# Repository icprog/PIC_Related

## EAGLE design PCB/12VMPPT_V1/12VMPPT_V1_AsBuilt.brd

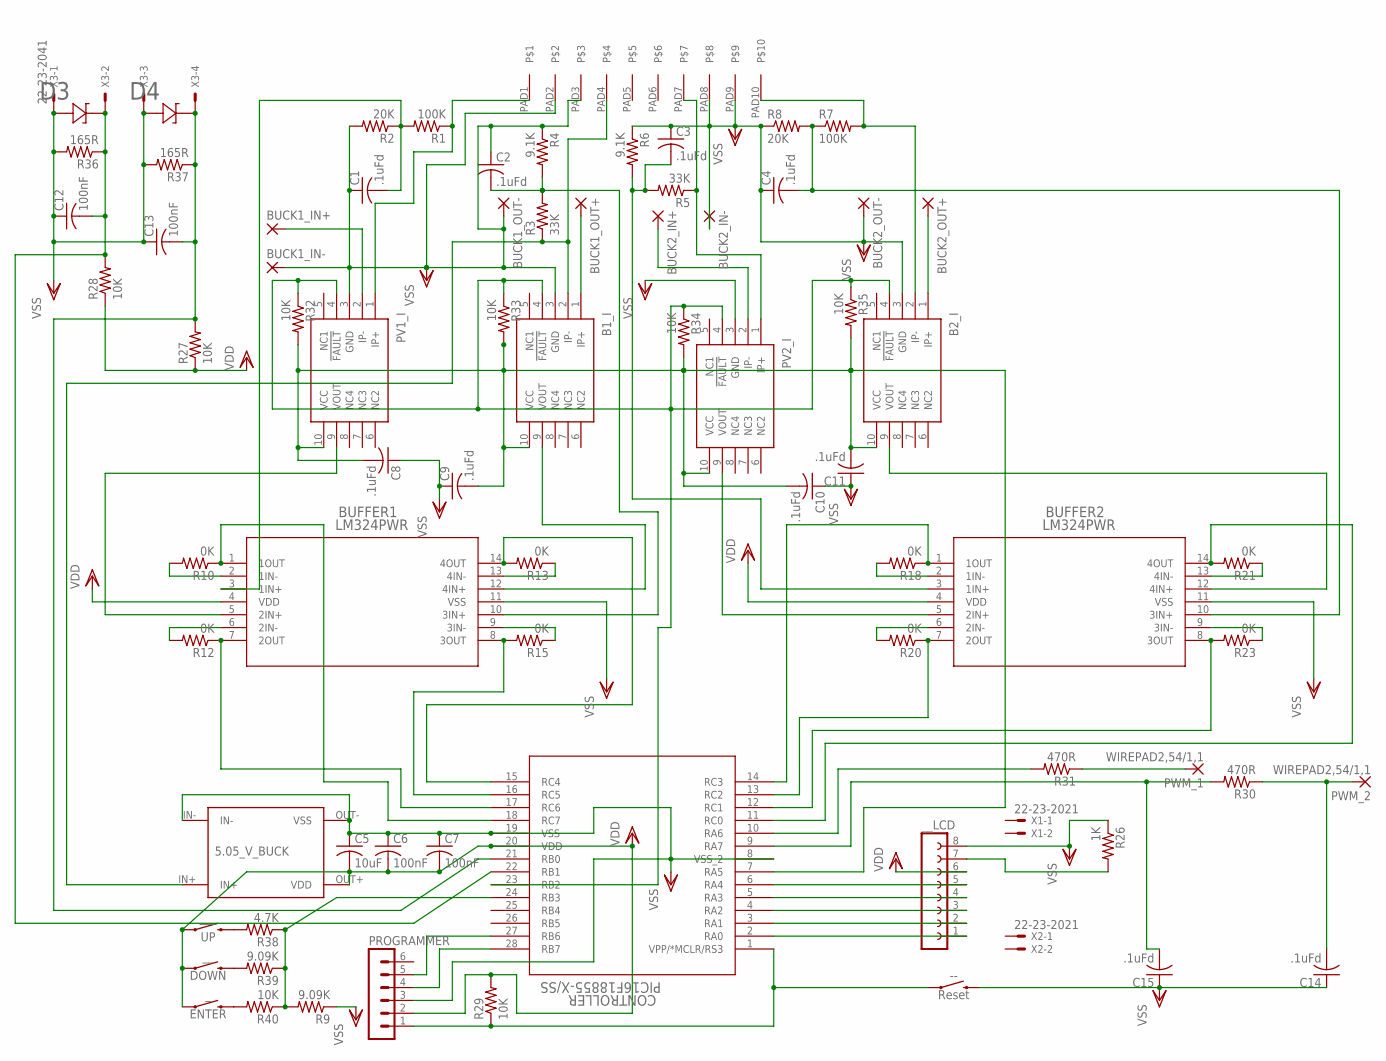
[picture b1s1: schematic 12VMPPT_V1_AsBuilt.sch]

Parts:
5.05_V_BUCK: TINY_BUCK
--: Reset; TACTILE_SWITCH_PTH_6.0MM
B1_I, B2_I: ACS711KEXLT-15AB-T; EX-PACKAGE
BUCK1_IN+, BUCK1_IN-, BUCK1_OUT+, BUCK1_OUT-, BUCK2_IN+, BUCK2_IN-, BUCK2_OUT+, BUCK2_OUT-: 3,81/1,4
BUFFER1, BUFFER2: LM324PWR; PW14
C1, C2, C3, C4, C8, C9, C10, C11, C14, C15: .1uFd; C0603
C5: 10uF; C0603
C6, C7, C12, C13: 100nF; C0603
CONTROLLER: PIC16F18855-X/SS; SSOP28_MC
D3, D4: CZRU52C3V3; CZRU
PROGRAMMER: MA06-1
PV1_I, PV2_I: ACS711KEXLT-15AB-T; EX-PACKAGE
PWM_1, PWM_2: WIREPAD2,54/1,1; 2,54/1,1
R1, R7: 100K; R0603
R2, R8: 20K; R0603
R3: 33K; R0603
R4, R6: 9.1K; R0603
R5: 33K; R1206
R9, R39: 9.09K; R0603
R10, R12, R13, R15, R18, R20, R21, R23: 0K; R0603
R26: 1K; R0603
R27, R32, R33: 10K; R1206
R28, R29, R34, R35, R40: 10K; R0603
R30: 470R; R0603
R31: 470R; R1206
R36, R37: 165R; R0603
R38: 4.7K; R0603
U$1: CONN-KF2EDG-10(5.08)E-BAYPLUGGABLECONNECTORS; CONN-KF2EDG-10(5.08)
X1, X2: 22-23-2021
X3: 22-23-2041
_: ENTER; TACTILE_SWITCH_PTH_6.0MM
__: DOWN; TACTILE_SWITCH_PTH_6.0MM
__LCD: FE08
___: UP; TACTILE_SWITCH_PTH_6.0MM

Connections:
BUCK_1OUT+: 5.05_V_BUCK.IN+, B1_I.2 (IP-), R3.1, U$1.PAD4
unnamed: BUCK1_IN+.1, PV1_I.2 (IP-)
unnamed: BUFFER1.5 (2IN+), PV1_I.9 (VOUT)
unnamed: BUFFER1.3 (1IN+), C1.2, R1.2, R2.1
unnamed: R38.2, ___.3 (2)
unnamed: BUFFER1.10 (3IN+), C2.2, R3.2, R4.2
unnamed: B1_I.9 (VOUT), BUFFER1.12 (4IN+)
unnamed: PV2_I.1 (IP+), R5.1, U$1.PAD7
unnamed: BUCK2_IN+.1, PV2_I.2 (IP-)
unnamed: R39.2, __.3 (2)
unnamed: B2_I.2 (IP-), R7.2, U$1.PAD10
unnamed: BUFFER2.10 (3IN+), C4.2, R7.1, R8.2
unnamed: B2_I.1 (IP+), BUCK2_OUT+.1
unnamed: BUFFER1.9 (3IN-), R15.1
unnamed: BUFFER1.1 (1OUT), CONTROLLER.18 (RC7), R10.1
unnamed: BUFFER1.6 (2IN-), R12.2
unnamed: BUFFER1.7 (2OUT), CONTROLLER.17 (RC6), R12.1
unnamed: BUFFER1.13 (4IN-), R13.1
unnamed: BUFFER1.2 (1IN-), R10.2
unnamed: BUFFER1.14 (4OUT), CONTROLLER.15 (RC4), R13.2
unnamed: BUFFER1.8 (3OUT), CONTROLLER.16 (RC5), R15.2
unnamed: B1_I.1 (IP+), BUCK1_OUT+.1
unnamed: CONTROLLER.2 (RA0), __LCD.1
unnamed: BUFFER2.1 (1OUT), CONTROLLER.14 (RC3), R18.1
unnamed: BUFFER2.7 (2OUT), CONTROLLER.13 (RC2), R20.1
unnamed: BUFFER2.6 (2IN-), R20.2
unnamed: BUFFER2.14 (4OUT), CONTROLLER.11 (RC0), R21.2
unnamed: BUFFER2.13 (4IN-), R21.1
unnamed: BUFFER2.8 (3OUT), CONTROLLER.12 (RC1), R23.2
unnamed: BUFFER2.9 (3IN-), R23.1
unnamed: BUFFER2.2 (1IN-), R18.2
unnamed: BUFFER2.5 (2IN+), PV2_I.9 (VOUT)
unnamed: B2_I.9 (VOUT), BUFFER2.12 (4IN+)
unnamed: CONTROLLER.3 (RA1), __LCD.2
unnamed: CONTROLLER.4 (RA2), __LCD.3
unnamed: CONTROLLER.5 (RA3), __LCD.4
unnamed: CONTROLLER.6 (RA4), __LCD.5
unnamed: R26.2, __LCD.7
unnamed: C12.2, CONTROLLER.22 (RB1), D3.1 (11), R28.2, R36.1, X3.2
unnamed: --.1, CONTROLLER.1 (VPP/*MCLR/RS3), PROGRAMMER.1, R29.1
unnamed: CONTROLLER.10 (RA6), R31.2
unnamed: C13.2, CONTROLLER.21 (RB0), D4.1 (11), R27.2, R37.1, X3.4
unnamed: C15.2, CONTROLLER.9 (RA7), R30.2
unnamed: CONTROLLER.28 (RB7), PROGRAMMER.4
unnamed: CONTROLLER.27 (RB6), PROGRAMMER.5
unnamed: C14.2, PWM_2.1, R30.1
unnamed: PWM_1.1, R31.1
unnamed: PV1_I.1 (IP+), R1.1, U$1.PAD1
unnamed: R40.2, _.3 (2)
unnamed: BUFFER2.3 (1IN+), C3.2, R5.2, R6.2
unnamed: B1_I.10 (VCC), B2_I.10 (VCC), C8.2, C9.2, C10.2, C11.2, CONTROLLER.7 (RA5), PV1_I.10 (VCC), PV2_I.10 (VCC), R32.2, R33.2, R34.2, R35.2
unnamed: B1_I.4 (!FAULT), B2_I.4 (!FAULT), CONTROLLER.23 (RB2), PV1_I.4 (!FAULT), PV2_I.4 (!FAULT), R32.1, R33.1, R34.1, R35.1
unnamed: CONTROLLER.24 (RB3), R9.2, R38.1, R39.1, R40.1
VDD: 5.05_V_BUCK.OUT+ (VDD), BUFFER1.4 (VDD), BUFFER2.4 (VDD), C5.2, C6.2, C7.2, CONTROLLER.20 (VDD), PROGRAMMER.2, R27.1, R28.1, R29.2, _.1, __.1, __LCD.6, ___.1
VSS: 5.05_V_BUCK.IN-, 5.05_V_BUCK.OUT- (VSS), --.3 (2), B1_I.3 (GND), B2_I.3 (GND), BUCK1_IN-.1, BUCK1_OUT-.1, BUCK2_IN-.1, BUCK2_OUT-.1, BUFFER1.11 (VSS), BUFFER2.11 (VSS), C1.1, C2.1, C3.1, C4.1, C5.1, C6.1, C7.1, C8.1, C9.1, C10.1, C11.1, C12.1, C13.1, C14.1, C15.1, CONTROLLER.8 (VSS_2), CONTROLLER.19 (VSS), D3.2 (22), D4.2 (22), PROGRAMMER.3, PV1_I.3 (GND), PV2_I.3 (GND), R2.2, R4.1, R6.1, R8.1, R9.1, R26.1, R36.2, R37.2, U$1.PAD2, U$1.PAD3, U$1.PAD8, U$1.PAD9, X3.1, X3.3, __LCD.8

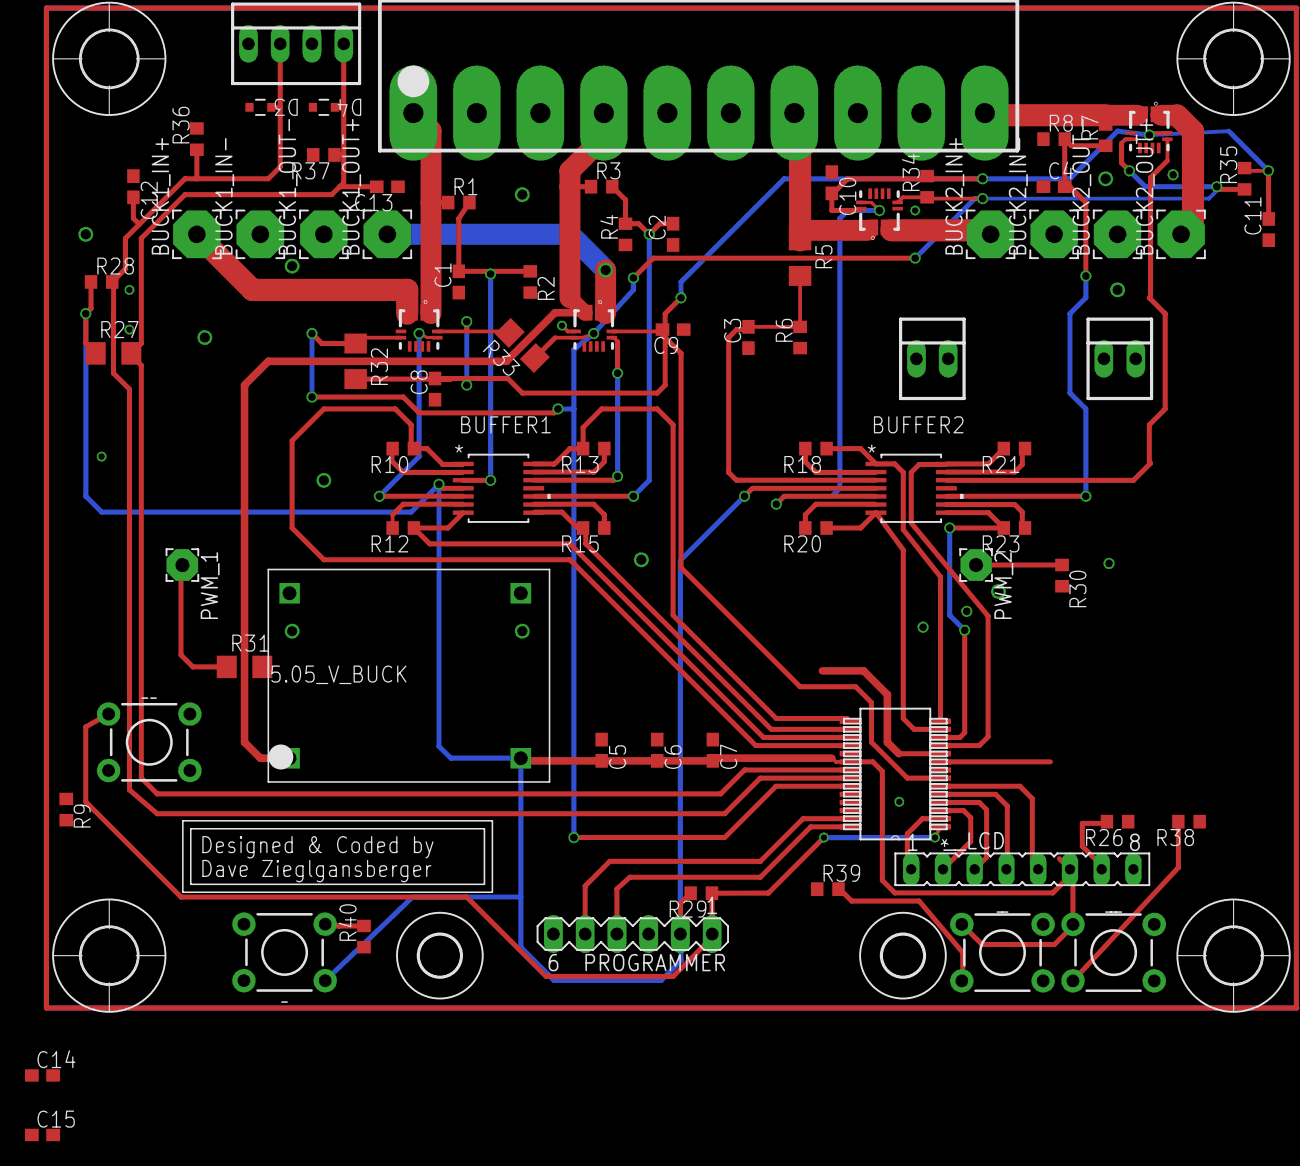
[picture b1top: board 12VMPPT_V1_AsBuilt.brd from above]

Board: 2 copper layers, 84 parts (0 on the bottom side), 55 nets.

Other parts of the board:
U$2, U$3, U$4, U$5: 4,5
U$7: DAVE
U$8, U$9: 3,3

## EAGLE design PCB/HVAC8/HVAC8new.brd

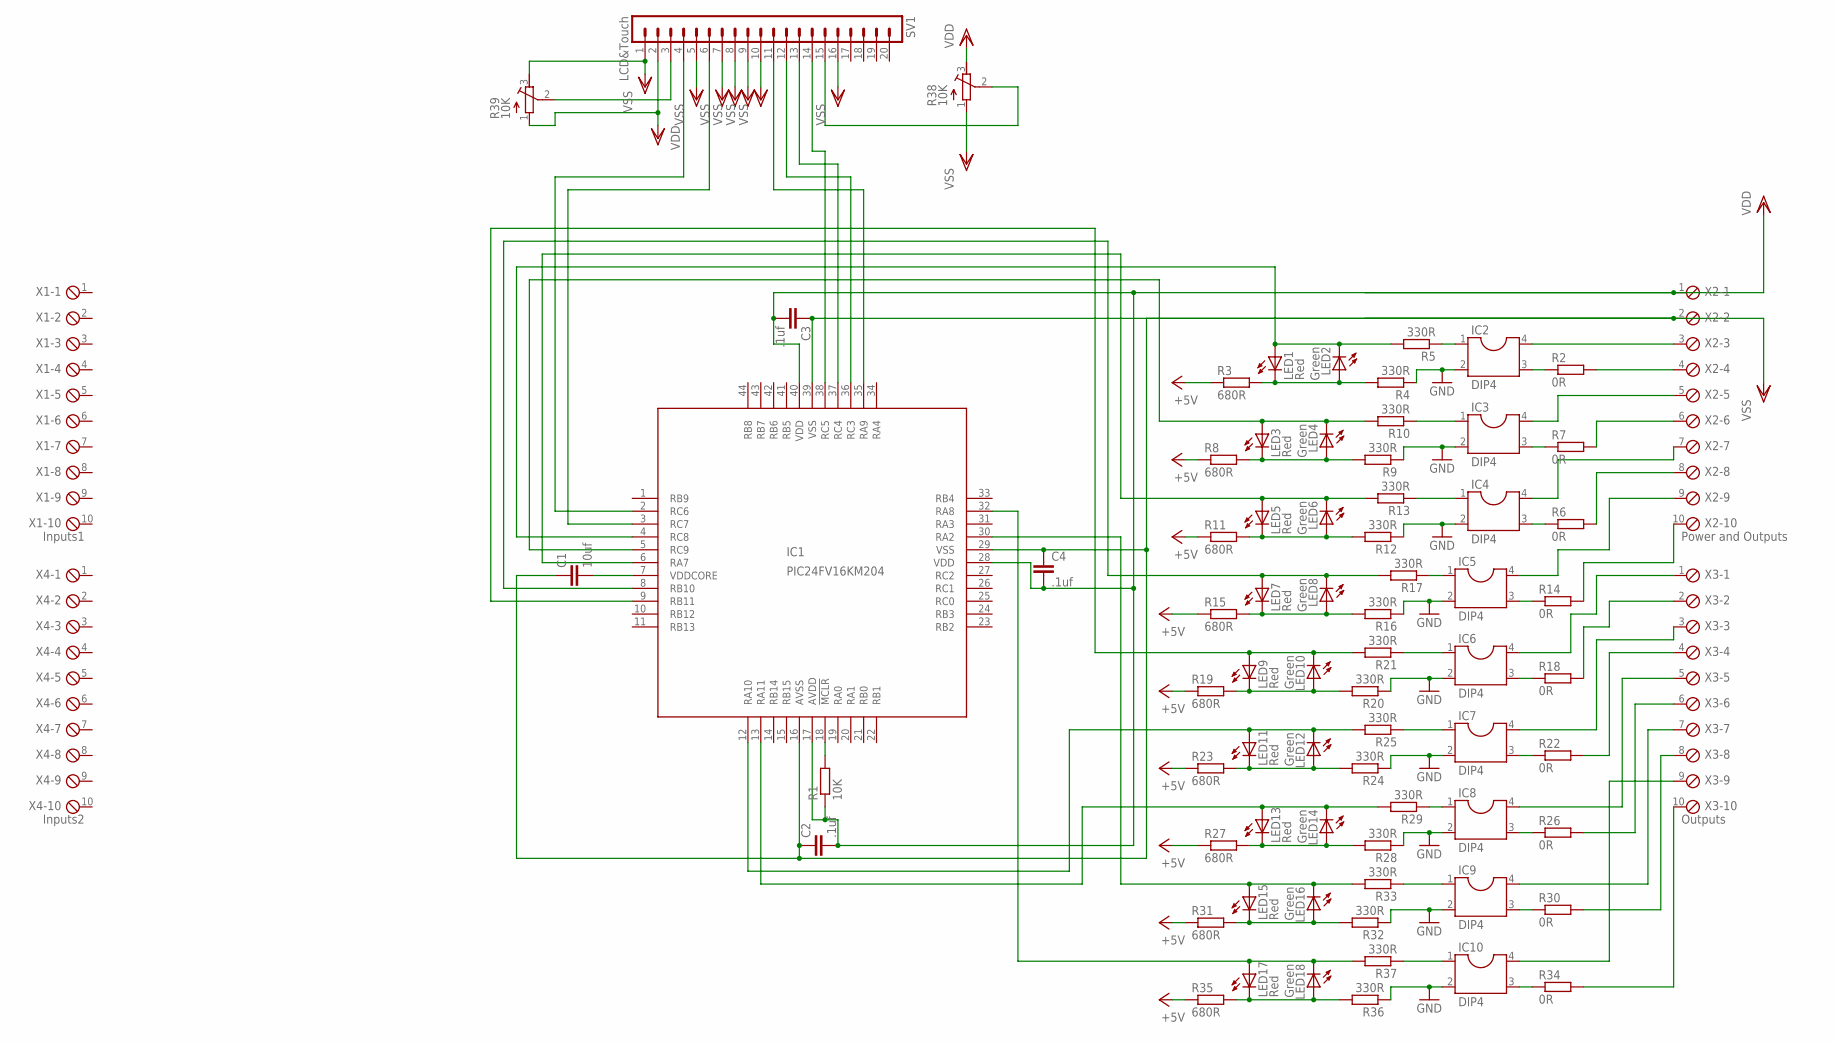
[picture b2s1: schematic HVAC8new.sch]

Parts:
C1: 10uf; C1206
C2, C3, C4: .1uf; C1206
IC1: PIC24FV16KM204; TQFP44
IC2, IC3, IC4, IC5, IC6, IC7, IC8, IC9, IC10: DIP4; SOCKET-04
LED1, LED3, LED5, LED7, LED9, LED11, LED13, LED15, LED17: Red; LED_1206
LED2, LED4, LED6, LED8, LED10, LED12, LED14, LED16, LED18: Green; LED_1206
R1: 10K; R1206
R2, R6, R7, R14, R18, R22, R26, R30, R34: 0R; R1206
R3, R8, R11, R15, R19, R23, R27, R31, R35: 680R; R1206
R4, R5, R9, R10, R12, R13, R16, R17, R20, R21, R24, R25, R28, R29, R32, R33, R36, R37: 330R; R1206
R38, R39: 10K; RTRIM3296W
SV1: LCD&Touch; MA20-1
X1: Inputs1; 10POL254
X2: Power and Outputs; 10POL254
X3: Outputs; 10POL254
X4: Inputs2; 10POL254

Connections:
+5V: R3.1, R8.1, R11.1, R15.1, R19.1, R23.1, R27.1, R31.1, R35.1
GND: IC2.2, IC3.2, IC4.2, IC5.2, IC6.2, IC7.2, IC8.2, IC9.2, IC10.2, R4.1, R9.1, R12.1, R16.1, R20.1, R24.1, R28.1, R32.1, R36.1
unnamed: C1.2, IC1.7 (VDDCORE)
unnamed: IC1.18 (!MCLR), R1.2
unnamed: IC2.1, R5.1
unnamed: IC1.5 (RC9), LED3.A, LED4.C, R10.2
unnamed: IC1.2 (RC6), SV1.4
unnamed: LED1.C, LED2.A, R3.2, R4.2
unnamed: IC2.3, R2.1
unnamed: IC3.1, R10.1
unnamed: IC3.4, X2.5
unnamed: R2.2, X2.4
unnamed: LED3.C, LED4.A, R8.2, R9.2
unnamed: IC3.3, R7.1
unnamed: IC2.4, X2.3
unnamed: R7.2, X2.6
unnamed: IC4.1, R13.1
unnamed: LED5.C, LED6.A, R11.2, R12.2
unnamed: IC4.3, R6.1
unnamed: IC1.6 (RA7), LED5.A, LED6.C, R13.2
unnamed: IC4.4, X2.7
unnamed: R6.2, X2.8
unnamed: IC5.1, R17.1
unnamed: LED7.C, LED8.A, R15.2, R16.2
unnamed: IC5.3, R14.1
unnamed: IC6.1, R21.1
unnamed: LED9.C, LED10.A, R19.2, R20.2
unnamed: IC6.3, R18.1
unnamed: IC5.4, X2.9
unnamed: R14.2, X2.10
unnamed: IC1.9 (RB11), LED9.A, LED10.C, R21.2
unnamed: IC6.4, X3.1
unnamed: R18.2, X3.2
unnamed: IC1.8 (RB10), LED7.A, LED8.C, R17.2
unnamed: IC7.1, R25.1
unnamed: LED11.C, LED12.A, R23.2, R24.2
unnamed: IC7.3, R22.1
unnamed: IC1.12 (RA10), LED11.A, LED12.C, R25.2
unnamed: IC7.4, X3.3
unnamed: R22.2, X3.4
unnamed: IC8.1, R29.1
unnamed: LED13.C, LED14.A, R27.2, R28.2
unnamed: IC8.3, R26.1
unnamed: IC9.1, R33.1
unnamed: LED15.C, LED16.A, R31.2, R32.2
unnamed: IC9.3, R30.1
unnamed: IC1.30 (RA2), LED15.A, LED16.C, R33.2
unnamed: IC1.13 (RA11), LED13.A, LED14.C, R29.2
unnamed: IC10.1, R37.1
unnamed: LED17.C, LED18.A, R35.2, R36.2
unnamed: IC10.3, R34.1
unnamed: IC1.32 (RA8), LED17.A, LED18.C, R37.2
unnamed: IC8.4, X3.5
unnamed: R26.2, X3.6
unnamed: IC9.4, X3.7
unnamed: R30.2, X3.8
unnamed: IC10.4, X3.9
unnamed: R34.2, X3.10
unnamed: IC1.4 (RC8), LED1.A, LED2.C, R5.2
unnamed: IC1.3 (RC7), SV1.6
unnamed: IC1.35 (RA9), SV1.11
unnamed: IC1.36 (RC3), SV1.12
unnamed: IC1.37 (RC4), SV1.13
unnamed: IC1.38 (RC5), SV1.14
unnamed: R39.2 (S), SV1.3
unnamed: R38.2 (S), SV1.15
VDD: C2.2, C3.2, C4.2, IC1.17 (AVDD), IC1.28 (VDD), IC1.40 (VDD), R1.1, R38.3 (E), R39.1 (A), SV1.2, X2.1
VSS: C1.1, C2.1, C3.1, C4.1, IC1.16 (AVSS), IC1.29 (VSS), IC1.39 (VSS), R38.1 (A), R39.3 (E), SV1.1, SV1.5, SV1.7, SV1.8, SV1.9, SV1.10, SV1.16, X2.2

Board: 2 copper layers, 76 parts (0 on the bottom side), 68 nets, no tracks yet.

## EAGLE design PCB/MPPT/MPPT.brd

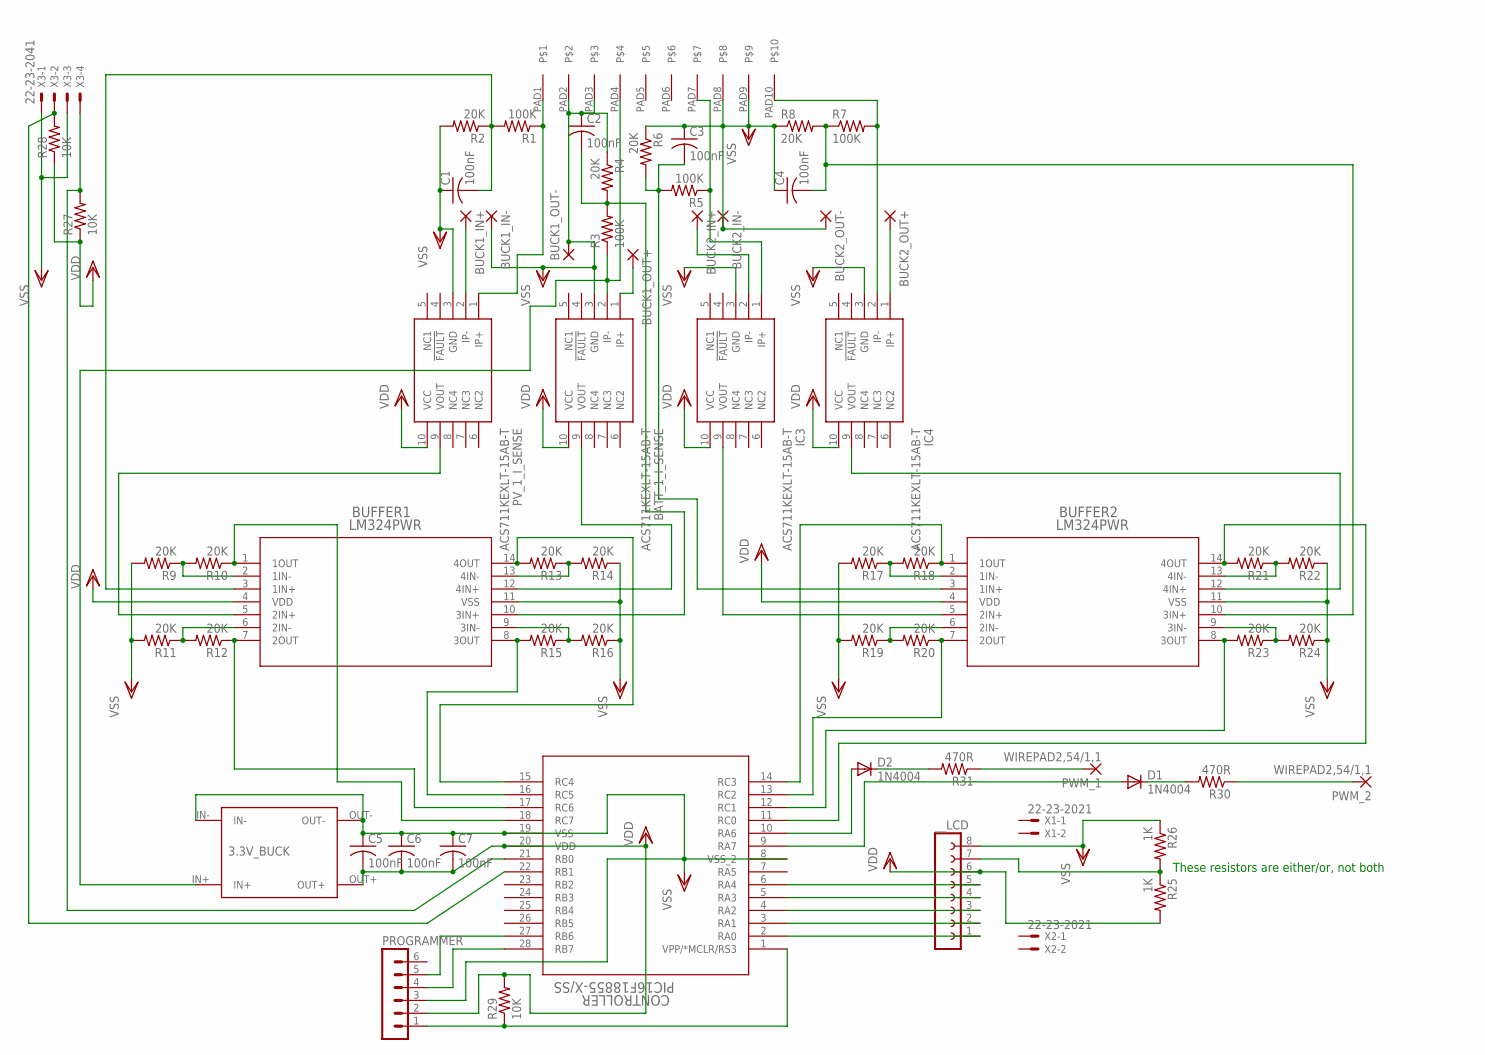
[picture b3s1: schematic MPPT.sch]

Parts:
3.3V_BUCK: TINY_BUCK
BATT_1_I_SENSE: ACS711KEXLT-15AB-T; EX-PACKAGE
BUCK1_IN+, BUCK1_IN-, BUCK1_OUT+, BUCK1_OUT-, BUCK2_IN+, BUCK2_IN-, BUCK2_OUT+, BUCK2_OUT-: 3,81/1,4
BUFFER1, BUFFER2: LM324PWR; PW14
C1, C2, C3, C4, C5, C6, C7: 100nF; C0603
CONTROLLER: PIC16F18855-X/SS; SSOP28_MC
D1, D2: 1N4004; DO41-10
IC3, IC4: ACS711KEXLT-15AB-T; EX-PACKAGE
PROGRAMMER: MA06-1
PV_1_I_SENSE: ACS711KEXLT-15AB-T; EX-PACKAGE
PWM_1, PWM_2: WIREPAD2,54/1,1; 2,54/1,1
R1, R3, R5, R7: 100K; R0603
R2, R4, R6, R8, R9, R10, R11, R12, R13, R14, R15, R16, R17, R18, R19, R20, R21, R22, R23, R24: 20K; R0603
R25, R26: 1K; R0603
R27: 10K; R1206
R28, R29: 10K; R0603
R30: 470R; R0603
R31: 470R; R1206
U$1: CONN-KF2EDG-10(5.08)E-BAYPLUGGABLECONNECTORS; CONN-KF2EDG-10(5.08)
X1, X2: 22-23-2021
X3: 22-23-2041
__LCD: FE08

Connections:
unnamed: PV_1_I_SENSE.1 (IP+), R1.1, U$1.PAD1
unnamed: BUFFER1.5 (2IN+), PV_1_I_SENSE.9 (VOUT)
unnamed: BUFFER1.3 (1IN+), C1.2, R1.2, R2.1
unnamed: BATT_1_I_SENSE.1 (IP+), BUCK1_OUT+.1
unnamed: BUFFER1.10 (3IN+), C2.2, R3.2, R4.2
unnamed: 3.3V_BUCK.IN+, BATT_1_I_SENSE.2 (IP-), R3.1, U$1.PAD4
unnamed: BUCK2_OUT+.1, IC4.1 (IP+)
unnamed: IC3.1 (IP+), R5.1, U$1.PAD7
unnamed: BUCK2_IN+.1, IC3.2 (IP-)
unnamed: BUFFER2.3 (1IN+), C3.2, R5.2, R6.2
unnamed: IC4.2 (IP-), R7.2, U$1.PAD10
unnamed: BUFFER2.10 (3IN+), C4.2, R7.1, R8.2
unnamed: BUCK1_IN+.1, PV_1_I_SENSE.2 (IP-)
unnamed: BUFFER1.9 (3IN-), R15.1, R16.2
unnamed: BUFFER1.1 (1OUT), CONTROLLER.18 (RC7), R10.1
unnamed: BUFFER1.6 (2IN-), R11.1, R12.2
unnamed: BUFFER1.7 (2OUT), CONTROLLER.17 (RC6), R12.1
unnamed: BUFFER1.13 (4IN-), R13.1, R14.2
unnamed: BUFFER1.2 (1IN-), R9.1, R10.2
unnamed: BUFFER1.14 (4OUT), CONTROLLER.15 (RC4), R13.2
unnamed: BUFFER1.8 (3OUT), CONTROLLER.16 (RC5), R15.2
unnamed: BATT_1_I_SENSE.9 (VOUT), BUFFER1.12 (4IN+)
unnamed: CONTROLLER.2 (RA0), __LCD.1
unnamed: BUFFER2.1 (1OUT), CONTROLLER.14 (RC3), R18.1
unnamed: BUFFER2.7 (2OUT), CONTROLLER.13 (RC2), R20.1
unnamed: BUFFER2.6 (2IN-), R19.1, R20.2
unnamed: BUFFER2.14 (4OUT), CONTROLLER.11 (RC0), R21.2
unnamed: BUFFER2.13 (4IN-), R21.1, R22.2
unnamed: BUFFER2.8 (3OUT), CONTROLLER.12 (RC1), R23.2
unnamed: BUFFER2.9 (3IN-), R23.1, R24.2
unnamed: BUFFER2.2 (1IN-), R17.1, R18.2
unnamed: BUFFER2.5 (2IN+), IC3.9 (VOUT)
unnamed: BUFFER2.12 (4IN+), IC4.9 (VOUT)
unnamed: CONTROLLER.3 (RA1), __LCD.2
unnamed: CONTROLLER.4 (RA2), __LCD.3
unnamed: CONTROLLER.5 (RA3), __LCD.4
unnamed: CONTROLLER.6 (RA4), __LCD.5
unnamed: R25.1, R26.2, __LCD.7
unnamed: CONTROLLER.22 (RB1), R28.2, X3.2
unnamed: CONTROLLER.1 (VPP/*MCLR/RS3), PROGRAMMER.1, R29.1
unnamed: CONTROLLER.10 (RA6), D2.A
unnamed: CONTROLLER.21 (RB0), R27.2, X3.4
unnamed: CONTROLLER.9 (RA7), D1.A
unnamed: CONTROLLER.28 (RB7), PROGRAMMER.4
unnamed: CONTROLLER.27 (RB6), PROGRAMMER.5
unnamed: PWM_2.1, R30.1
unnamed: D1.C, R30.2
unnamed: PWM_1.1, R31.1
unnamed: D2.C, R31.2
VDD: 3.3V_BUCK.OUT+, BATT_1_I_SENSE.10 (VCC), BUFFER1.4 (VDD), BUFFER2.4 (VDD), C5.2, C6.2, C7.2, CONTROLLER.20 (VDD), IC3.10 (VCC), IC4.10 (VCC), PROGRAMMER.2, PV_1_I_SENSE.10 (VCC), R25.2, R27.1, R28.1, R29.2, __LCD.6
VSS: 3.3V_BUCK.IN-, 3.3V_BUCK.OUT-, BATT_1_I_SENSE.3 (GND), BUCK1_IN-.1, BUCK1_OUT-.1, BUCK2_IN-.1, BUCK2_OUT-.1, BUFFER1.11 (VSS), BUFFER2.11 (VSS), C1.1, C2.1, C3.1, C4.1, C5.1, C6.1, C7.1, CONTROLLER.8 (VSS_2), CONTROLLER.19 (VSS), IC3.3 (GND), IC4.3 (GND), PROGRAMMER.3, PV_1_I_SENSE.3 (GND), R2.2, R4.1, R6.1, R8.1, R9.2, R11.2, R14.1, R16.1, R17.2, R19.2, R22.1, R24.1, R26.1, U$1.PAD2, U$1.PAD3, U$1.PAD8, U$1.PAD9, X3.1, X3.3, __LCD.8

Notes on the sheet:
These resistors are either/or, not both

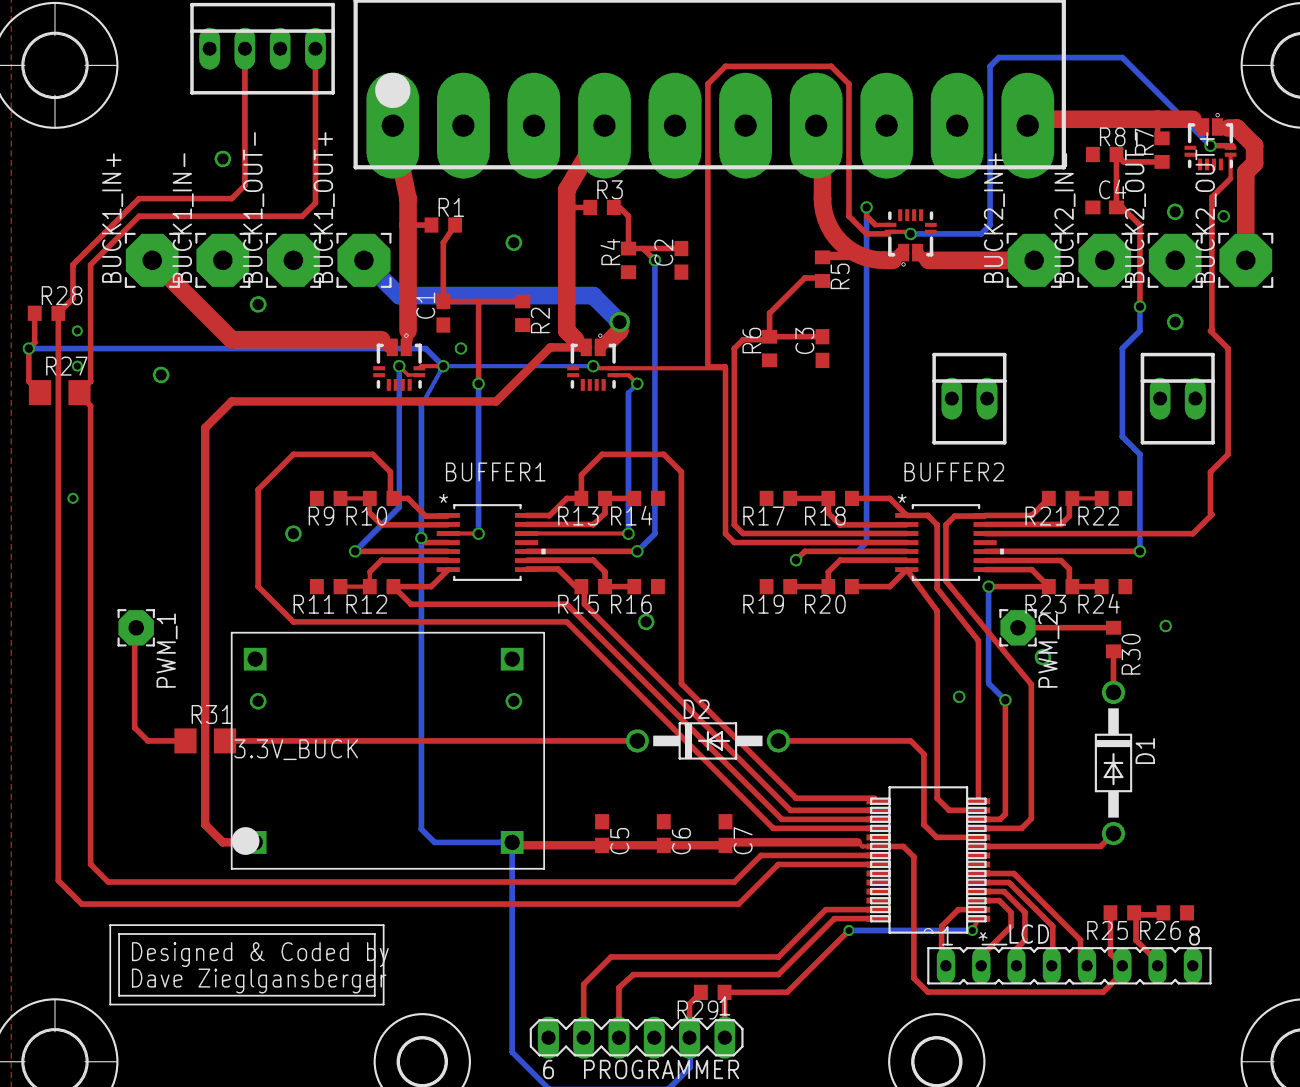
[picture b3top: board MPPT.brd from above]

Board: 2 copper layers, 71 parts (0 on the bottom side), 51 nets.

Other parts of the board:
U$2, U$3, U$4, U$5: 4,5
U$7: DAVE
U$8, U$9: 3,3

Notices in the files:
parts and their libraries:
SparkFun-Switches: Licensing: Creative Commons ShareAlike 4.0 International - https://creativecommons.org/licenses/by-sa/4.0
COPYRIGHT: Copyright (C) 2016 Accelerated Designs. All rights reserved
